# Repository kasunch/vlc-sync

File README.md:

# Harmony: A Time Synchronisation System for VLC Access Points

## About
This repository contains the implementation files for the paper titled **Harmony: A Time Synchronisation System for Visible Light Communication Access Points** published in ACM SenSys 2022. Access the paper here.

## Electronic Hardware

The electronic hardware consists of three modules.
* OWC Receiver module
* OWC Transmitter module
* ADC & DAC module

## Digital Hardware

The digital hardware implementation is done in Verilog.

**Note:**

The electronic and digital hardware implementations are fast-developed prototypes. Therefore, the implementations have several places which can be optimised.

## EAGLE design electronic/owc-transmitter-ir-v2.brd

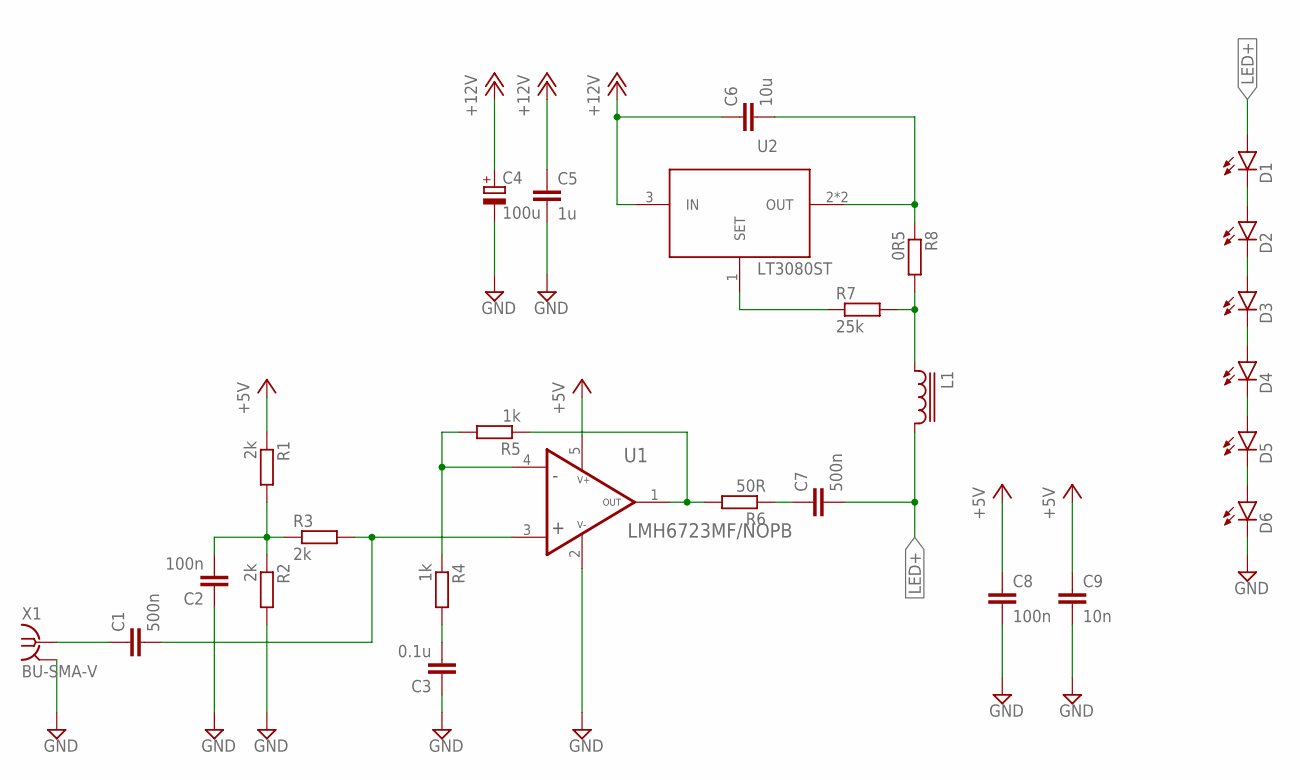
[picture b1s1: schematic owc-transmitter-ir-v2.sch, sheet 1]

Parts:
C1, C7: 500n; C0805
C2, C8: 100n; C0805
C3: 0.1u; C0805
C4: 100u; CT3528
C5: 1u; C0805
C6: 10u; C0805
C9: 10n; C0805
D1, D2, D3, D4, D5, D6: LED5MM
L1: SRR6603
R1, R2, R3: 2k; R0805
R4, R5: 1k; R0805
R6: 50R; R0805
R7: 25k; R0805
R8: 0R5; R0805
U1: LMH6723MF/NOPB; SOT23-5L
U2: LT3080ST; SOT223
X1: BU-SMA-V

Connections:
+5V: C8.1, C9.1, R1.1, U1.5 (V+); also elsewhere on the board
+12V: C4.+, C5.1, C6.1, U2.3 (IN); also elsewhere on the board
GND: C2.1, C3.1, C4.-, C5.2, C8.2, C9.2, D6.K (C), R2.2, U1.2 (V-), X1.2, X1.3 (2), X1.4 (2), X1.5 (2); also elsewhere on the board
LED+: C7.2, D1.A, L1.P$2 (2)
unnamed: D1.K (C), D2.A
unnamed: D2.K (C), D3.A
unnamed: D3.K (C), D4.A
unnamed: D4.K (C), D5.A
unnamed: D5.K (C), D6.A
unnamed: R5.1, R6.2, U1.1 (OUT)
unnamed: C7.1, R6.1
unnamed: R4.1, R5.2, U1.4 (IN-)
unnamed: C6.2, R8.1, U2.2 (OUT), U2.4 (OUT)
unnamed: C3.2, R4.2
unnamed: L1.P$1 (1), R7.2, R8.2
unnamed: C2.2, R1.2, R2.1, R3.1
unnamed: C1.1, X1.1
unnamed: R7.1, U2.1 (SET)
unnamed: C1.2, R3.2, U1.3 (IN+)

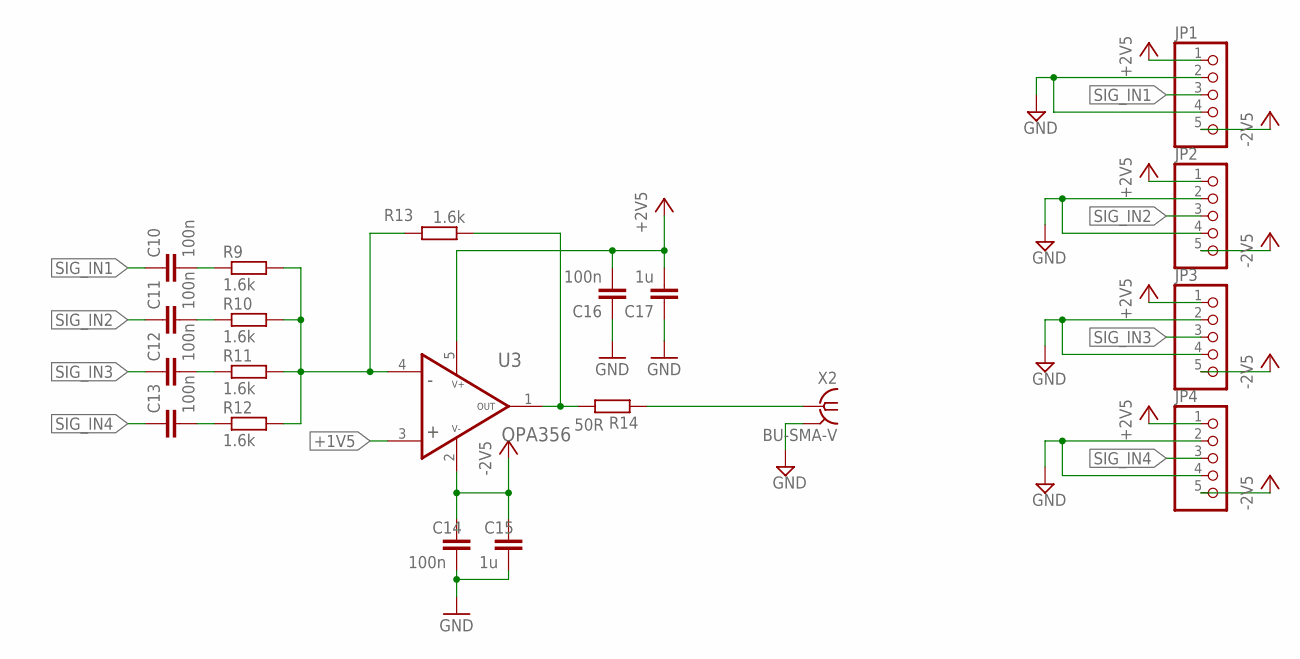
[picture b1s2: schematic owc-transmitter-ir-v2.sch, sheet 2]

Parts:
C10, C11, C12, C13, C14, C16: 100n; C0805
C15, C17: 1u; C0805
JP1, JP2, JP3, JP4: PINHD-1X5; 1X05
R9, R10, R11, R12, R13: 1.6k; R0805
R14: 50R; R0805
U3: OPA356; SOT23-5L
X2: BU-SMA-V

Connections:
+1V5: U3.3 (IN+); also elsewhere on the board
+2V5: C16.2, C17.2, JP1.1, JP2.1, JP3.1, JP4.1, U3.5 (V+); also elsewhere on the board
-2V5: C14.1, C15.1, JP1.5, JP2.5, JP3.5, JP4.5, U3.2 (V-); also elsewhere on the board
GND: C14.2, C15.2, C16.1, C17.1, JP1.2, JP1.4, JP2.2, JP2.4, JP3.2, JP3.4, JP4.2, JP4.4, X2.2, X2.3 (2), X2.4 (2), X2.5 (2); also elsewhere on the board
unnamed: R13.1, R14.2, U3.1 (OUT)
unnamed: C12.2, R11.1
unnamed: R9.2, R10.2, R11.2, R12.2, R13.2, U3.4 (IN-)
unnamed: R14.1, X2.1
unnamed: C11.2, R10.1
unnamed: C13.2, R12.1
unnamed: C10.2, R9.1
SIG_IN1: C10.1, JP1.3
SIG_IN2: C11.1, JP2.3
SIG_IN3: C12.1, JP3.3
SIG_IN4: C13.1, JP4.3

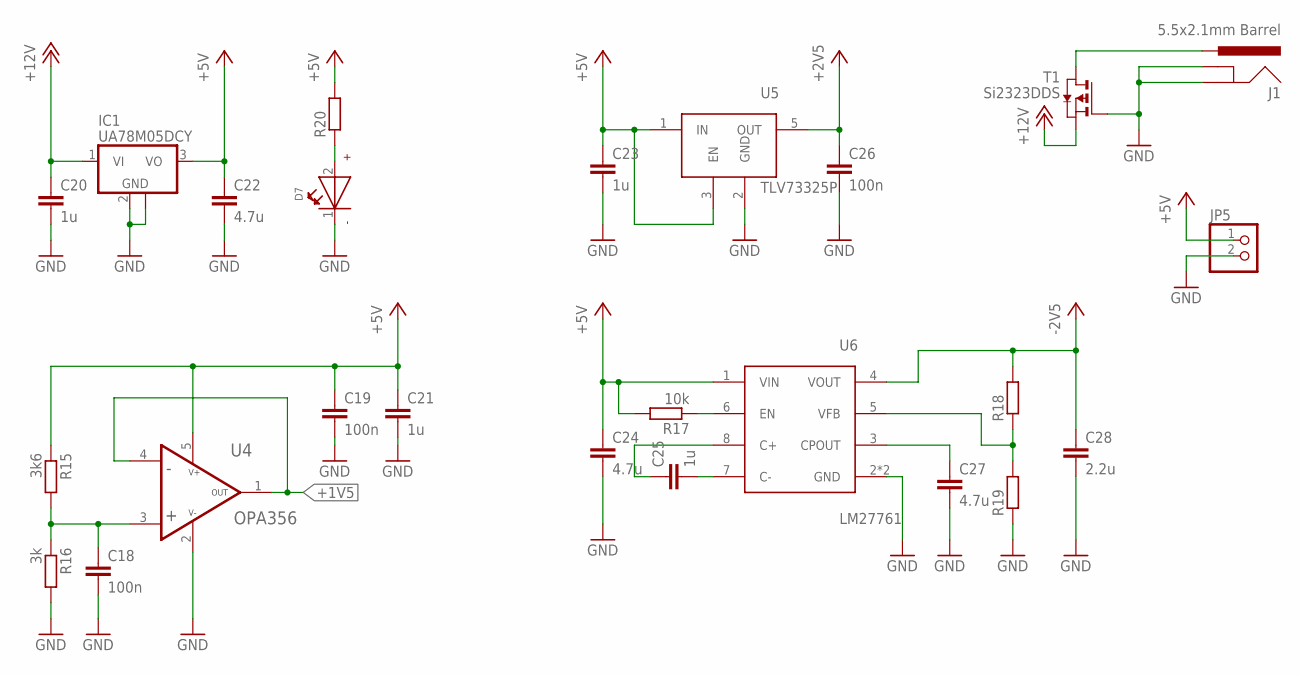
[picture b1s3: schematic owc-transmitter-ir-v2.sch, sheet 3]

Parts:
C18, C19, C26: 100n; C0805
C20, C21, C23, C25: 1u; C0805
C22, C24, C27: 4.7u; C0805
C28: 2.2u; C0805
D7: WL-SMCW-150080GS75000-G; WL-SMCW_0805
IC1: UA78M05DCY; SOT223
J1: 5.5x2.1mm Barrel; POWER_JACK_SMD
JP5: PINHD-1X2; 1X02
R15: 3k6; R0805
R16: 3k; R0805
R17: 10k; R0805
R18, R19, R20: R-EU_R0805; R0805
T1: Si2323DDS; SOT-23
U4: OPA356; SOT23-5L
U5: TLV73325P; SOT23-5L
U6: LM27761DSG; WSON-8-PAD; MPN LM27761DSGT

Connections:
+1V5: U4.1 (OUT), U4.4 (IN-); also elsewhere on the board
+2V5: C26.1, U5.5 (OUT); also elsewhere on the board
+5V: C19.1, C21.1, C22.1, C23.1, C24.1, IC1.3 (VO), JP5.1, R15.1, R17.2, R20.2, U4.5 (V+), U5.1 (IN), U5.3 (EN), U6.1 (VIN); also elsewhere on the board
+12V: C20.1, IC1.1 (VI), T1.2 (S); also elsewhere on the board
-2V5: C28.1, R18.2, U6.4 (VOUT); also elsewhere on the board
GND: C18.2, C19.2, C20.2, C21.2, C22.2, C23.2, C24.2, C26.2, C27.2, C28.2, D7.1 (-), IC1.2 (GND), IC1.4 (GND), J1.GND (GNDBREAK), J1.P$4 (GND), JP5.2, R16.2, R19.1, T1.3 (G), U4.2 (V-), U5.2 (GND), U6.2 (GND), U6.PAD (GND); also elsewhere on the board
unnamed: C27.1, U6.3 (CPOUT)
unnamed: C25.1, U6.8 (C+)
unnamed: C25.2, U6.7 (C-)
unnamed: D7.2 (+), R20.1
unnamed: R17.1, U6.6 (EN)
unnamed: R18.1, R19.2, U6.5 (VFB)
unnamed: C18.1, R15.2, R16.1, U4.3 (IN+)
unnamed: J1.VIN0 (PWR), T1.1 (D)

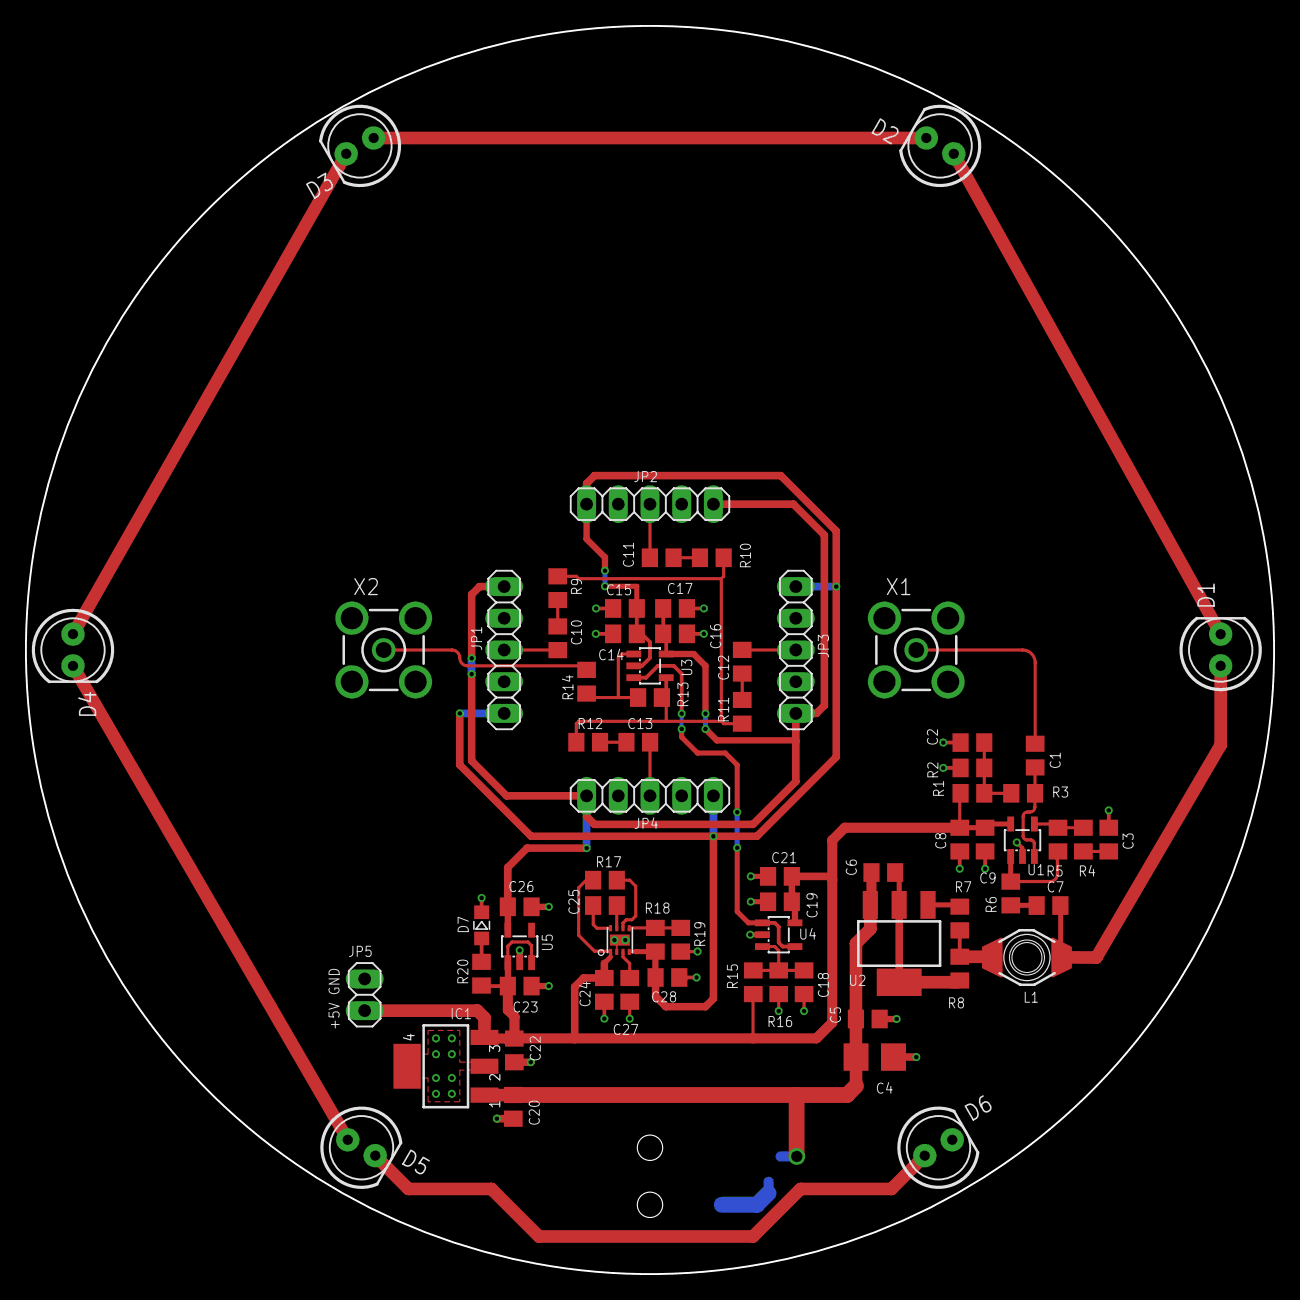
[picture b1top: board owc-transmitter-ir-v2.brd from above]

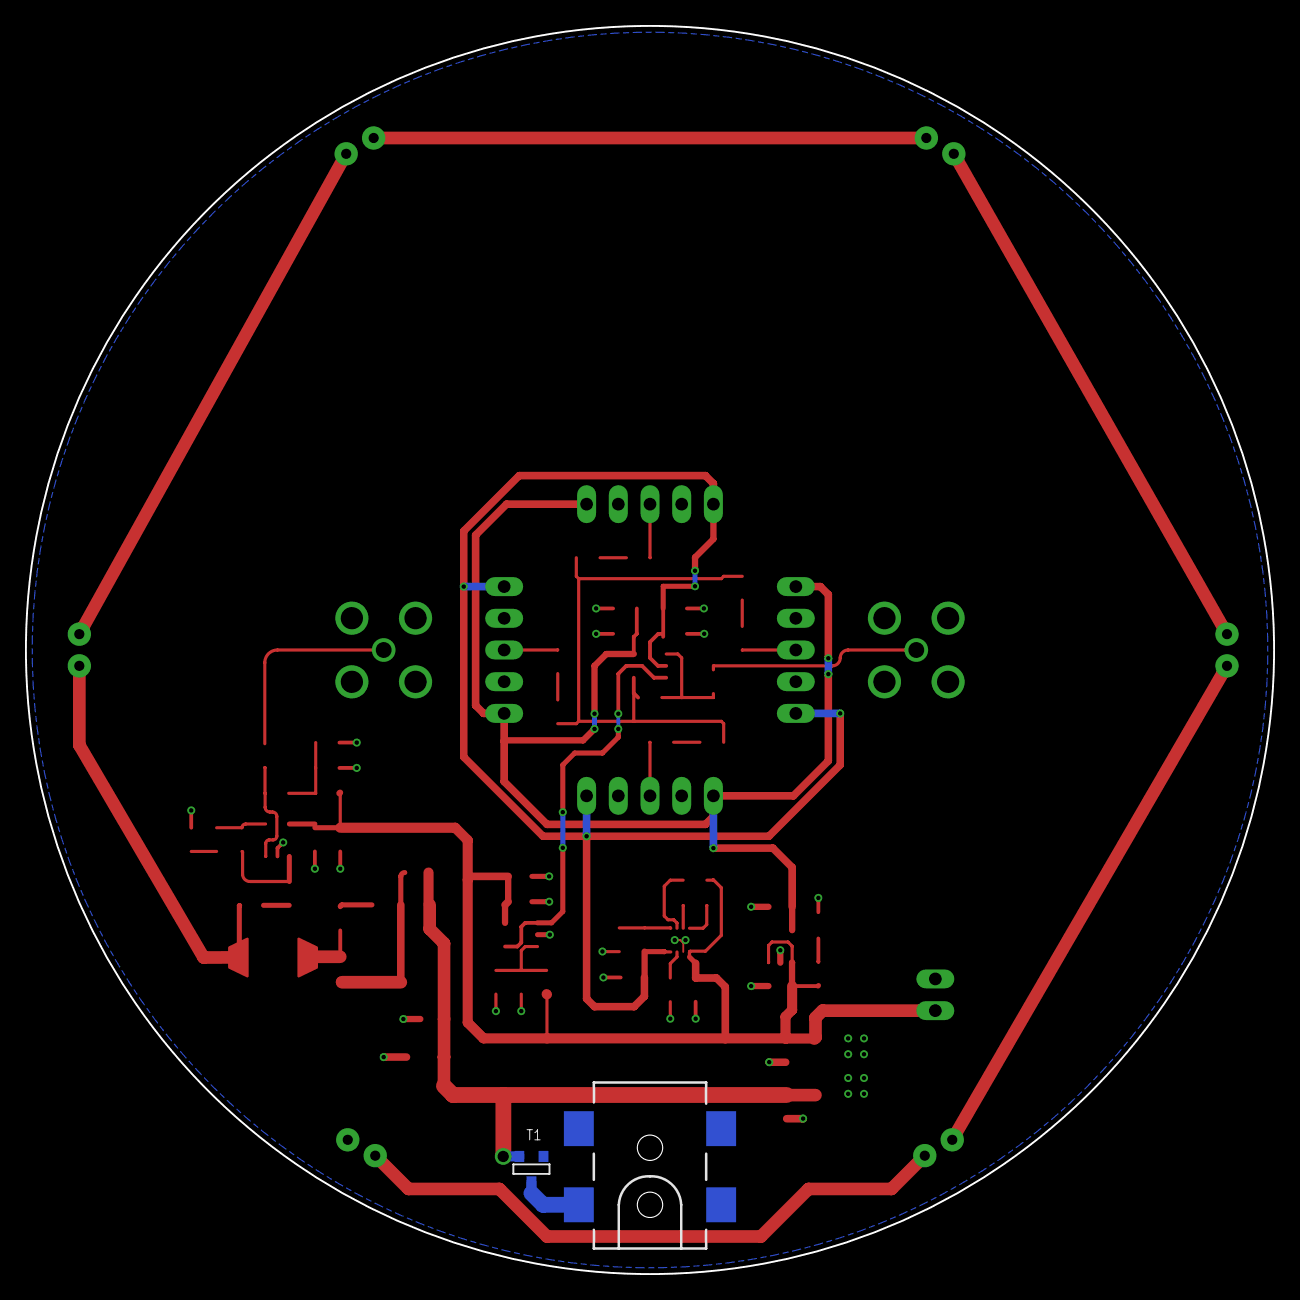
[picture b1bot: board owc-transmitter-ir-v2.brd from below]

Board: 2 copper layers, 100.0 x 100.0 mm, 72 parts (2 on the bottom side), 41 nets.

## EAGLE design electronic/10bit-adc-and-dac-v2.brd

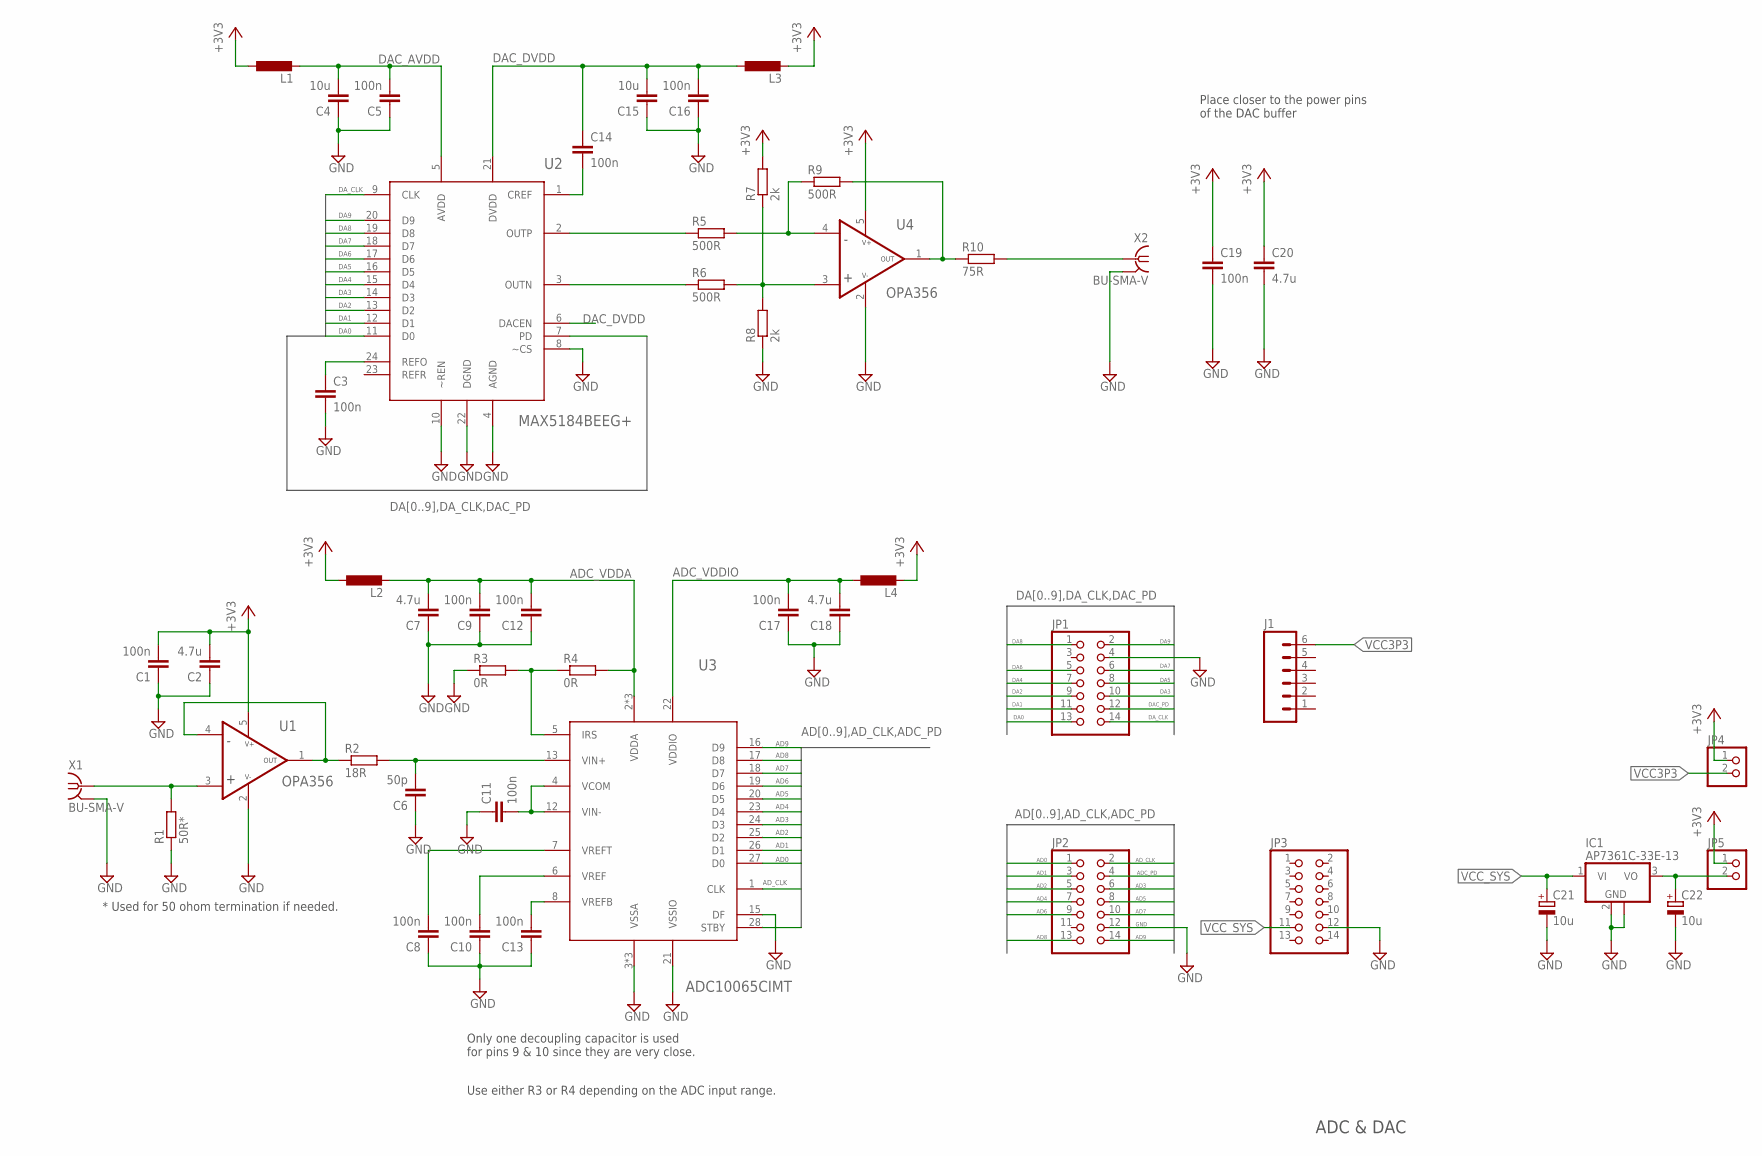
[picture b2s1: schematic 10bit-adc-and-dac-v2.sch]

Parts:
C1, C3, C5, C8, C9, C10, C11, C12, C13, C14, C16, C17, C19: 100n; C0805
C2, C7, C18, C20: 4.7u; C0805
C4, C15: 10u; C0805
C6: 50p; C0805
C21, C22: 10u; CT3528
IC1: AP7361C-33E-13; SOT223; MPN AP7361C-33E-13
J1: M06SILK_FEMALE_PTH; 1X06
JP1, JP2, JP3: PINHD-2X7; 2X07
JP4, JP5: PINHD-1X2; 1X02
L1, L2, L3, L4: L-EUL2012C; L2012C; MPN CIM21J252NE
R1: 50R*; R0805
R2: 18R; R0805
R3, R4: 0R; R0805
R5, R6, R9: 500R; R0805
R7, R8: 2k; R0805
R10: 75R; R0805
U1, U4: OPA356; SOT23-5L; MPN OPA356AIDBVR
U2: MAX5184BEEG+; SOP63P600X175-24N; MPN MAX5184BEEG+
U3: ADC10065CIMT; TSSOP28; MPN ADC10065CIMTX/NOPB
X1, X2: BU-SMA-V; MPN 5-1814832-1

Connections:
+3V3: C1.2, C2.2, C19.1, C20.1, JP4.1, JP5.1, L1.1, L2.1, L3.2, L4.2, R7.2, U1.5 (V+), U4.5 (V+)
AD0: JP2.1, U3.27 (D0)
AD1: JP2.3, U3.26 (D1)
AD2: JP2.5, U3.25 (D2)
AD3: JP2.6, U3.24 (D3)
AD4: JP2.7, U3.23 (D4)
AD5: JP2.8, U3.20 (D5)
AD6: JP2.9, U3.19 (D6)
AD7: JP2.10, U3.18 (D7)
AD8: JP2.13, U3.17 (D8)
AD9: JP2.14, U3.16 (D9)
ADC_PD: JP2.4, U3.28 (STBY)
ADC_VDDA: C7.2, C9.2, C12.2, L2.2, R4.2, U3.2 (VDDA), U3.9 (VDDA), U3.10 (VDDA)
ADC_VDDIO: C17.2, C18.2, L4.1, U3.22 (VDDIO)
AD_CLK: JP2.2, U3.1 (CLK)
DA0: JP1.13, U2.11 (D0)
DA1: JP1.11, U2.12 (D1)
DA2: JP1.9, U2.13 (D2)
DA3: JP1.10, U2.14 (D3)
DA4: JP1.7, U2.15 (D4)
DA5: JP1.8, U2.16 (D5)
DA6: JP1.5, U2.17 (D6)
DA7: JP1.6, U2.18 (D7)
DA8: JP1.1, U2.19 (D8)
DA9: JP1.2, U2.20 (D9)
DAC_AVDD: C4.2, C5.2, L1.2, U2.5 (AVDD)
DAC_DVDD: C14.1, C15.2, C16.2, L3.1, U2.6 (DACEN), U2.21 (DVDD)
DAC_PD: JP1.12, U2.7 (PD)
DA_CLK: JP1.14, U2.9 (CLK)
GND: C1.1, C2.1, C3.2, C4.1, C5.1, C6.1, C7.1, C8.1, C9.1, C10.1, C11.1, C12.1, C13.1, C15.1, C16.1, C17.1, C18.1, C19.2, C20.2, C21.-, C22.-, IC1.2 (GND), IC1.4 (GND), JP1.4, JP2.12, JP3.12, R1.1, R3.1, R8.1, U1.2 (V-), U2.4 (AGND), U2.8 (~CS), U2.10 (~REN), U2.22 (DGND), U3.3 (VSSA), U3.11 (VSSA), U3.14 (VSSA), U3.15 (DF), U3.21 (VSSIO), U4.2 (V-), X1.2, X1.3 (2), X1.4 (2), X1.5 (2), X2.2, X2.3 (2), X2.4 (2), X2.5 (2)
unnamed: R2.1, U1.1 (OUT), U1.4 (IN-)
unnamed: R10.2, X2.1
unnamed: R1.2, U1.3 (IN+), X1.1
unnamed: C22.+, IC1.3 (VO), JP5.2
unnamed: R3.2, R4.1, U3.5 (IRS)
unnamed: C13.2, U3.8 (VREFB)
unnamed: C6.2, R2.2, U3.13 (VIN+)
unnamed: C10.2, U3.6 (VREF)
unnamed: C3.1, U2.24 (REFO)
unnamed: C14.2, U2.1 (CREF)
unnamed: C8.2, U3.7 (VREFT)
unnamed: C11.2, U3.4 (VCOM), U3.12 (VIN-)
unnamed: R9.2, R10.1, U4.1 (OUT)
unnamed: R6.2, R7.1, R8.2, U4.3 (IN+)
unnamed: R5.2, R9.1, U4.4 (IN-)
unnamed: R5.1, U2.2 (OUTP)
unnamed: R6.1, U2.3 (OUTN)
VCC3P3: J1.6, JP4.2
VCC_SYS: C21.+, IC1.1 (VI), JP3.11

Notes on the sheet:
Place closer to the power pins of the DAC buffer
Only one decoupling capacitor is used for pins 9 & 10 since they are very close.
ADC & DAC
* Used for 50 ohom termination if needed.
Use either R3 or R4 depending on the ADC input range.

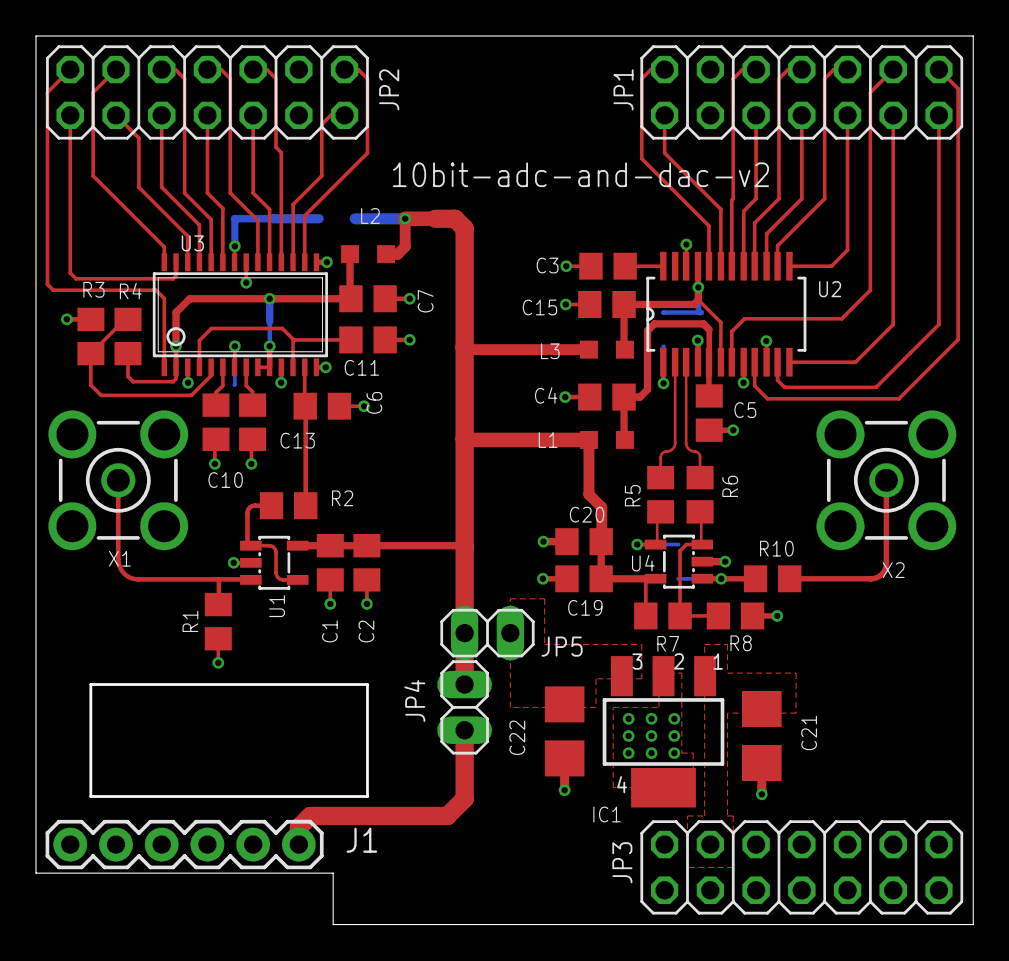
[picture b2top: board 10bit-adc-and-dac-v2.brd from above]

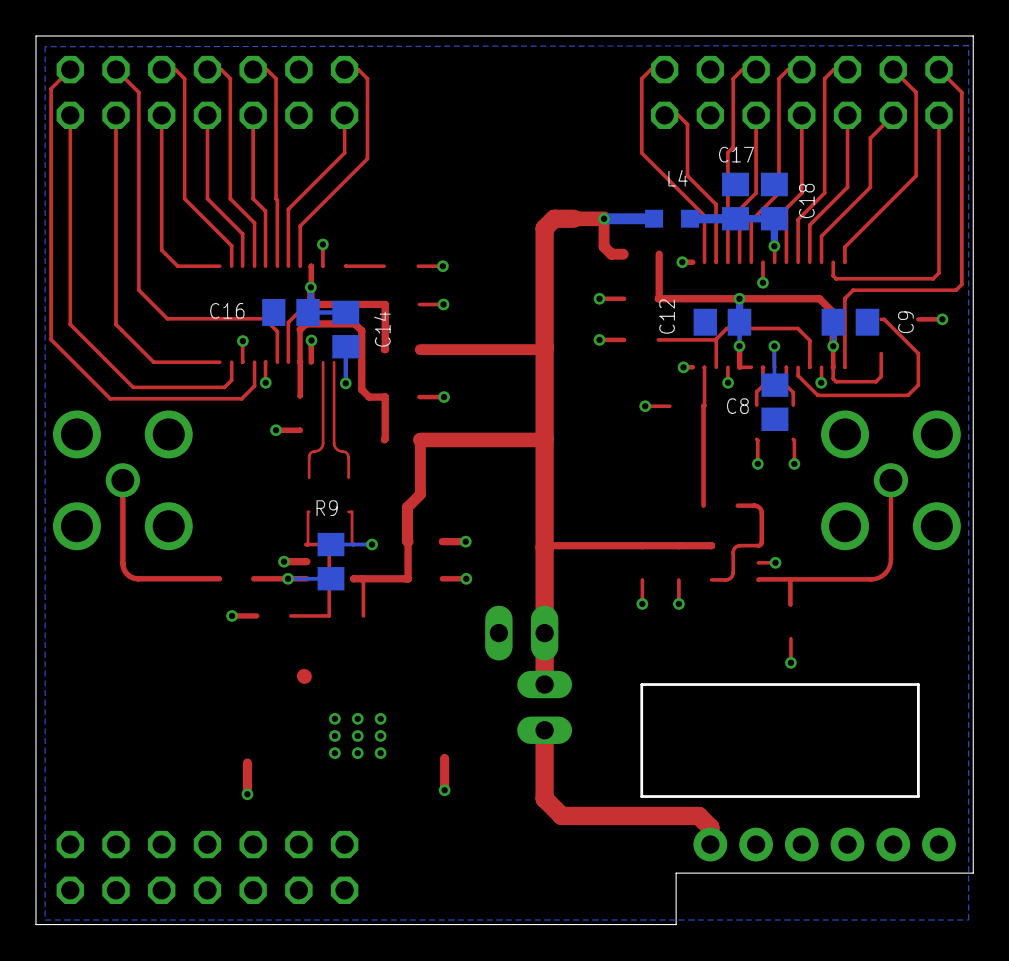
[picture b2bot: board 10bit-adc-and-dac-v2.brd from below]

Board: 2 copper layers, 51.9 x 49.2 mm, 49 parts (9 on the bottom side), 49 nets.

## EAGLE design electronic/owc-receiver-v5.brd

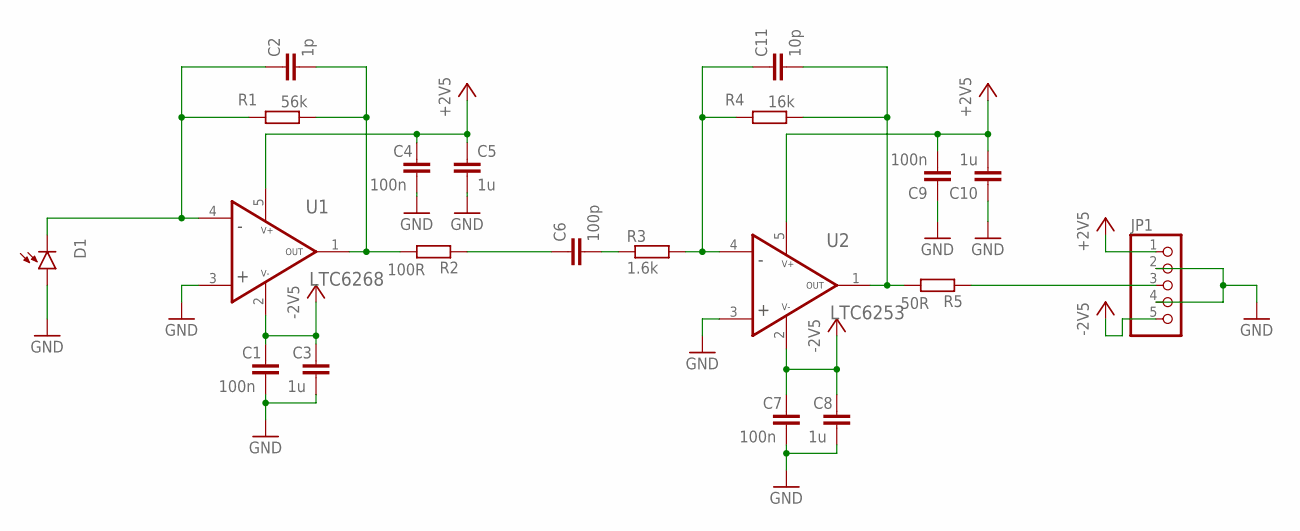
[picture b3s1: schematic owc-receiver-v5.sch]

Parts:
C1, C4, C7, C9: 100n; C0805
C2: 1p; C0805
C3, C5, C8, C10: 1u; C0805
C6: 100p; C0805
C11: 10p; C0805
D1: PHOTODIODE5MM; LED5MM
JP1: PINHD-1X5; 1X05
R1: 56k; R0805
R2: 100R; R0805
R3: 1.6k; R0805
R4: 16k; R0805
R5: 50R; R0805
U1: LTC6268; SOT23-5L
U2: LTC6253; SOT23-5L

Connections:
+2V5: C4.1, C5.1, C9.2, C10.2, JP1.1, U1.5 (V+), U2.5 (V+)
-2V5: C1.1, C3.1, C7.1, C8.1, JP1.5, U1.2 (V-), U2.2 (V-)
GND: C1.2, C3.2, C4.2, C5.2, C7.2, C8.2, C9.1, C10.1, D1.A, JP1.2, JP1.4, U1.3 (IN+), U2.3 (IN+)
unnamed: C11.2, R4.1, R5.2, U2.1 (OUT)
unnamed: C2.2, R1.1, R2.2, U1.1 (OUT)
unnamed: C6.1, R2.1
unnamed: C6.2, R3.1
unnamed: C2.1, D1.K (C), R1.2, U1.4 (IN-)
unnamed: C11.1, R3.2, R4.2, U2.4 (IN-)
unnamed: JP1.3, R5.1

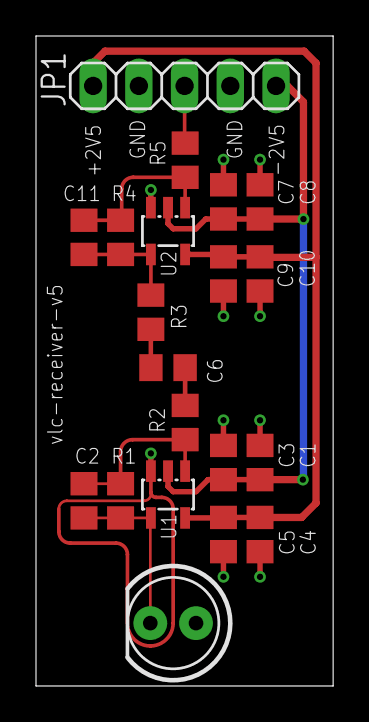
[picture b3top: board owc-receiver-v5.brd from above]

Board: 2 copper layers, 16.5 x 36.1 mm, 20 parts (0 on the bottom side), 10 nets.

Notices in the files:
parts and their libraries:
SparkFun-Connectors: Licensing: Creative Commons ShareAlike 4.0 International - https://creativecommons.org/licenses/by-sa/4.0
Wurth_Elektronik_Optoelectronics_rev17b: Copyright: Würth Elektronik
